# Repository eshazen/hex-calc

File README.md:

# hex-calc

Simple Hex/Binary/Decimal calculator inspired by HP-16C and TI Programmer.

[large image](pix/front.jpg)

Features:

* Hex / Decimal / Binary display in signed or unsigned mode
  * Entire stack for 8/16 bits, two levels for 32 bits
* four-function two-compliment or unsigned arithmetic
* 8 / 16 / 32 / 64 bit word size
* four-level RPN stack with roll / swap

Runs on ATMeg328 at 8MHz.  Power is 4xAA batteries regulated to 5V.
Industry-standard 16x2 backlit LCD.  Three LEDs:

* Power
* f key (function/shift) active
* signed display mode

Code in <tt>src/calc_hw</tt>.

KiCAD design in <tt>keyboard-pcb</tt>.
<br>Schematic:  [keyboard-pcb.pdf](keyboard-pcb/keyboard-pcb.pdf)

See https://github.com/eshazen/calc-demo-xwin for an X-windows
app written in C which illustrates the general idea.

## Enhancements

Thinking about some added features to support fractional arithmetic
for woodworking.  Display options to round to nearest fraction (1/4,
1/8, 1/16, 1/32, 1/64) and switch between decimal inch, fraction inch
and decimal mm.  Ft/inches another useful display option.

This would involve either floating point or scaled integer math.
For this application the range is pretty limited, maybe 8 ft (~100 in)
max.

Base units could be 2.54e-6 in (1um).  100 inches would require ~25
bits.

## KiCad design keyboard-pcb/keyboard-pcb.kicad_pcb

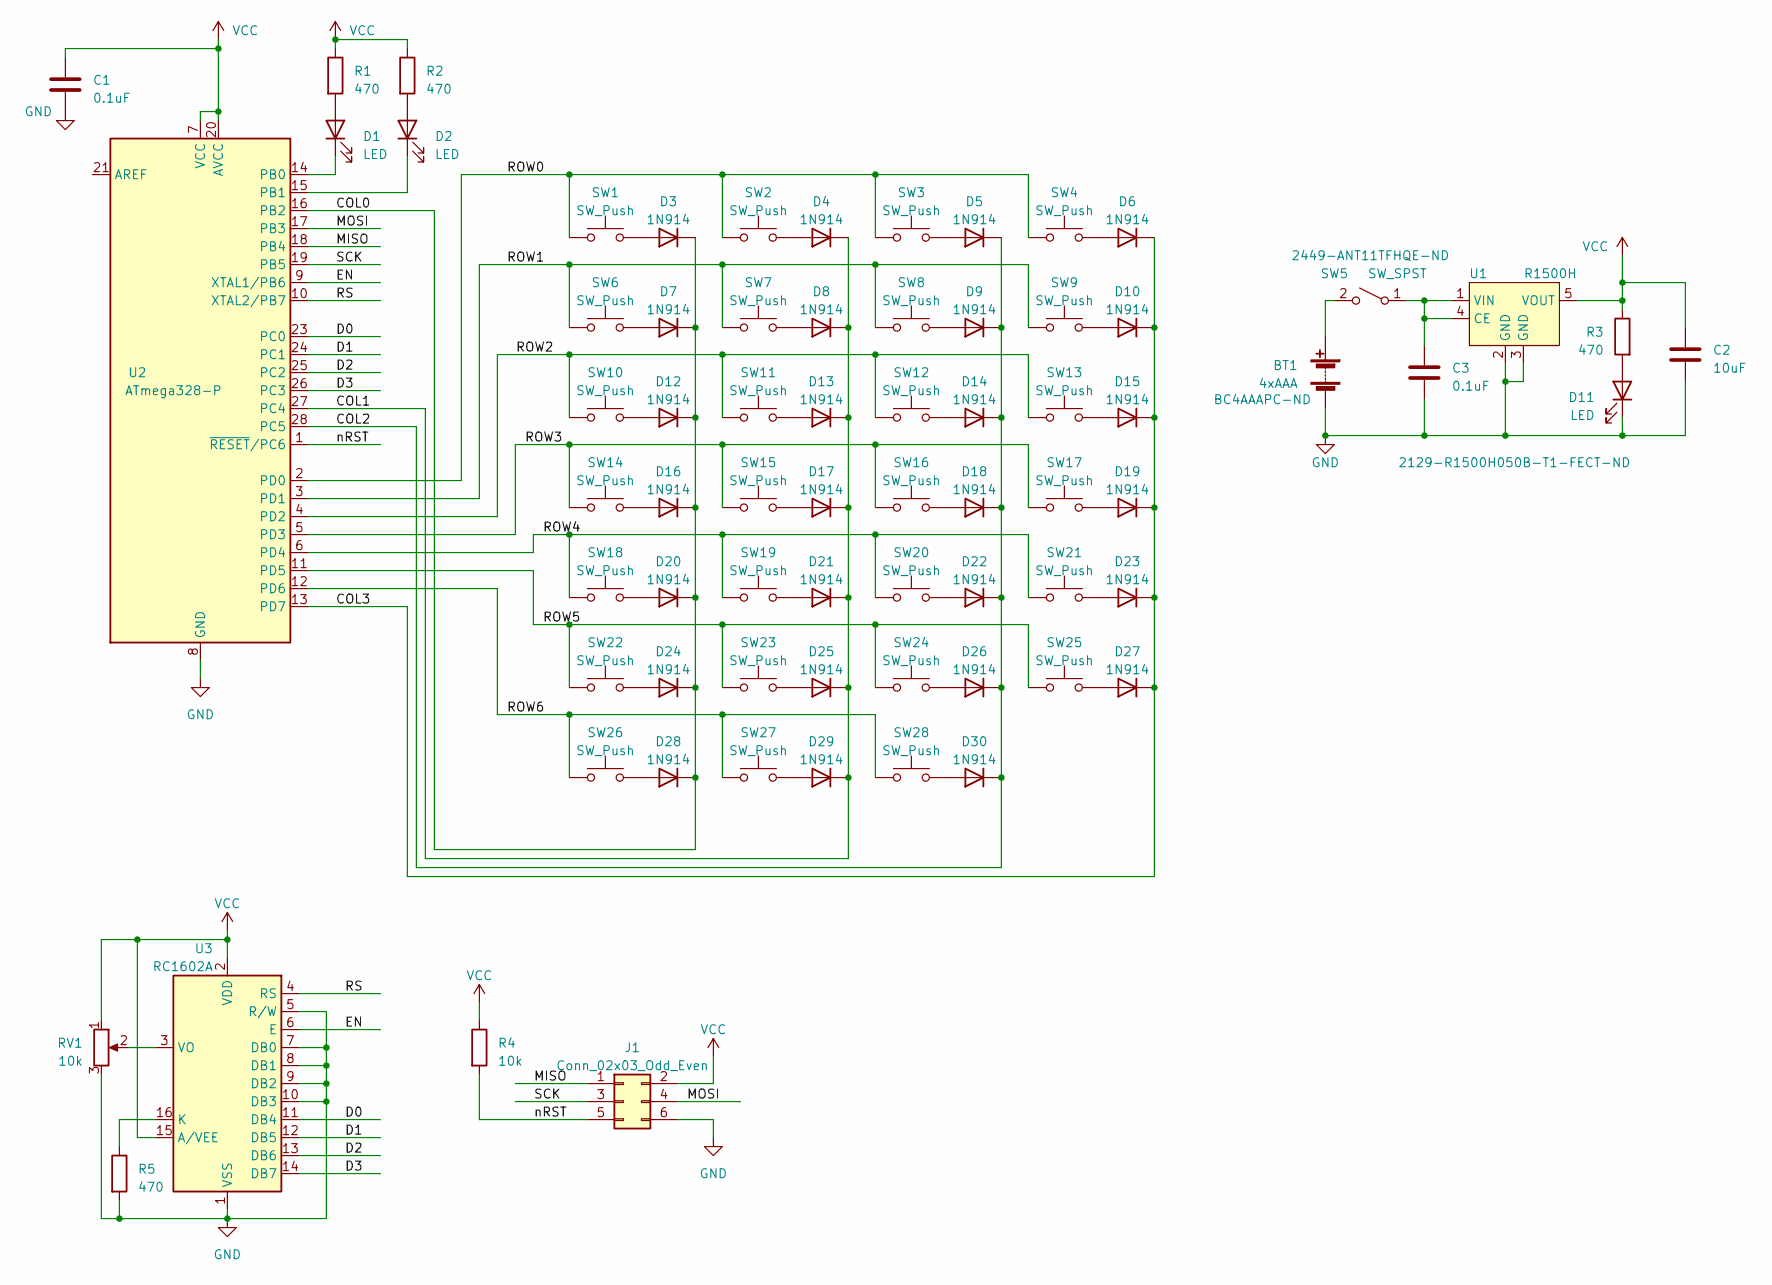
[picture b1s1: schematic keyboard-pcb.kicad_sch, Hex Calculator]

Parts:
BT1: 4xAAA; Keystone_4xAAA_2481
C1, C3: 0.1uF; C_Disc_D5.0mm_W2.5mm_P2.50mm
C2: 10uF; C_Disc_D5.0mm_W2.5mm_P2.50mm
D1, D2, D11: LED; LED_D3.0mm
D3, D4, D5, D6, D7, D8, D9, D10, D12, D13, D14, D15, D16, D17, D18, D19, D20, D21, D22, D23, D24, D25, D26, D27, D28, D29, D30: 1N914; D_DO-35_SOD27_P7.62mm_Horizontal
J1: Conn_02x03_Odd_Even; PinHeader_2x03_P2.54mm_Vertical
R1, R2, R3, R5: 470; R_Axial_DIN0207_L6.3mm_D2.5mm_P7.62mm_Horizontal
R4: 10k; R_Axial_DIN0207_L6.3mm_D2.5mm_P7.62mm_Horizontal
RV1: 10k; Potentiometer_Bourns_3266P_Horizontal
SW1, SW2, SW3, SW4, SW6, SW7, SW8, SW9, SW10, SW11, SW12, SW13, SW14, SW15, SW16, SW17, SW18, SW19, SW20, SW21, SW22, SW23, SW24, SW25, SW26, SW27: SW_Push; SW_Cherry_MX_1.00u_PCB
SW5: SW_SPST; ANT11TFHQE_switch
SW28: SW_Push; SW_Cherry_MX_2.00u_PCB
U1: R1500H; SOT-89-5_Handsoldering
U2: ATmega328-P; DIP-28_W7.62mm
U3: RC1602A; WC1602A

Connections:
/COL0: D3.1 (K), D7.1 (K), D12.1 (K), D16.1 (K), D20.1 (K), D24.1 (K), D28.1 (K), U2.16 (PB2)
/COL1: D4.1 (K), D8.1 (K), D13.1 (K), D17.1 (K), D21.1 (K), D25.1 (K), D29.1 (K), U2.27 (PC4)
/COL2: D5.1 (K), D9.1 (K), D14.1 (K), D18.1 (K), D22.1 (K), D26.1 (K), D30.1 (K), U2.28 (PC5)
/COL3: D6.1 (K), D10.1 (K), D15.1 (K), D19.1 (K), D23.1 (K), D27.1 (K), U2.13 (PD7)
/D0: U2.23 (PC0), U3.11 (DB4)
/D1: U2.24 (PC1), U3.12 (DB5)
/D2: U2.25 (PC2), U3.13 (DB6)
/D3: U2.26 (PC3), U3.14 (DB7)
/EN: U2.9 (XTAL1/PB6), U3.6 (E)
/MISO: J1.1, U2.18 (PB4)
/MOSI: J1.4, U2.17 (PB3)
/ROW0: SW1.1, SW2.1, SW3.1, SW4.1, U2.2 (PD0)
/ROW1: SW6.1, SW7.1, SW8.1, SW9.1, U2.3 (PD1)
/ROW2: SW10.1, SW11.1, SW12.1, SW13.1, U2.4 (PD2)
/ROW3: SW14.1, SW15.1, SW16.1, SW17.1, U2.5 (PD3)
/ROW4: SW18.1, SW19.1, SW20.1, SW21.1, U2.6 (PD4)
/ROW5: SW22.1, SW23.1, SW24.1, SW25.1, U2.11 (PD5)
/ROW6: SW26.1, SW27.1, SW28.1, U2.12 (PD6)
/RS: U2.10 (XTAL2/PB7), U3.4 (RS)
/SCK: J1.3, U2.19 (PB5)
/nRST: J1.5, R4.2, U2.1 (~RESET/PC6)
GND: BT1.2 (-), C1.2, C2.2, C3.2, D11.1 (K), J1.6, R5.2, RV1.3, U1.2 (GND), U1.3 (GND), U2.8 (GND), U2.22 (GND), U3.1 (VSS), U3.5 (R/W), U3.7 (DB0), U3.8 (DB1), U3.9 (DB2), U3.10 (DB3)
unnamed: BT1.1 (+), SW5.2 (B)
unnamed: D1.2 (A), R1.2
unnamed: D1.1 (K), U2.14 (PB0)
unnamed: D2.2 (A), R2.2
unnamed: D2.1 (K), U2.15 (PB1)
unnamed: D3.2 (A), SW1.2
unnamed: D4.2 (A), SW2.2
unnamed: D5.2 (A), SW3.2
unnamed: D6.2 (A), SW4.2
unnamed: D7.2 (A), SW6.2
unnamed: D8.2 (A), SW7.2
unnamed: D9.2 (A), SW8.2
unnamed: D10.2 (A), SW9.2
unnamed: D11.2 (A), R3.2
unnamed: D12.2 (A), SW10.2
unnamed: D13.2 (A), SW11.2
unnamed: D14.2 (A), SW12.2
unnamed: D15.2 (A), SW13.2
unnamed: D16.2 (A), SW14.2
unnamed: D17.2 (A), SW15.2
unnamed: D18.2 (A), SW16.2
unnamed: D19.2 (A), SW17.2
unnamed: D20.2 (A), SW18.2
unnamed: D21.2 (A), SW19.2
unnamed: D22.2 (A), SW20.2
unnamed: D23.2 (A), SW21.2
unnamed: D24.2 (A), SW22.2
unnamed: D25.2 (A), SW23.2
unnamed: D26.2 (A), SW24.2
unnamed: D27.2 (A), SW25.2
unnamed: D28.2 (A), SW26.2
unnamed: D29.2 (A), SW27.2
unnamed: D30.2 (A), SW28.2
unnamed: C3.1, SW5.1 (A), U1.1 (VIN), U1.4 (CE)
unnamed: R5.1, U3.16 (K)
unnamed: RV1.2, U3.3 (VO)
VCC: C1.1, C2.1, J1.2, R1.1, R2.1, R3.1, R4.1, RV1.1, U1.5 (VOUT), U2.7 (VCC), U2.20 (AVCC), U3.2 (VDD), U3.15 (A/VEE)

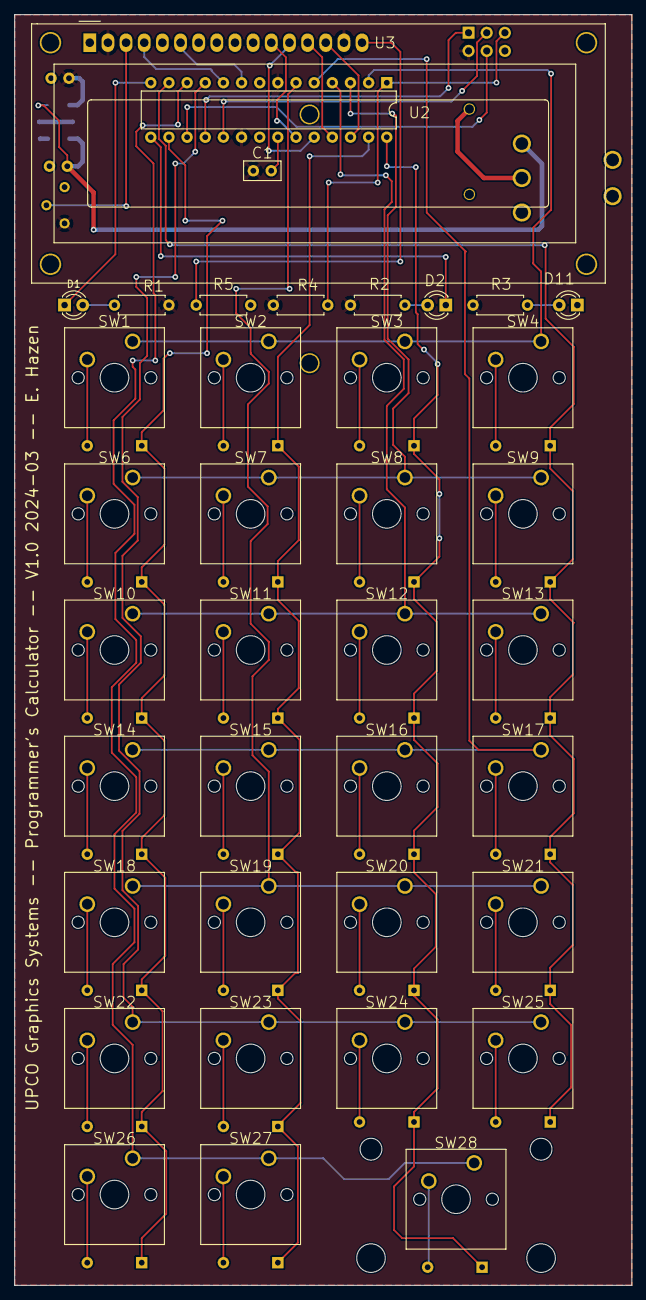
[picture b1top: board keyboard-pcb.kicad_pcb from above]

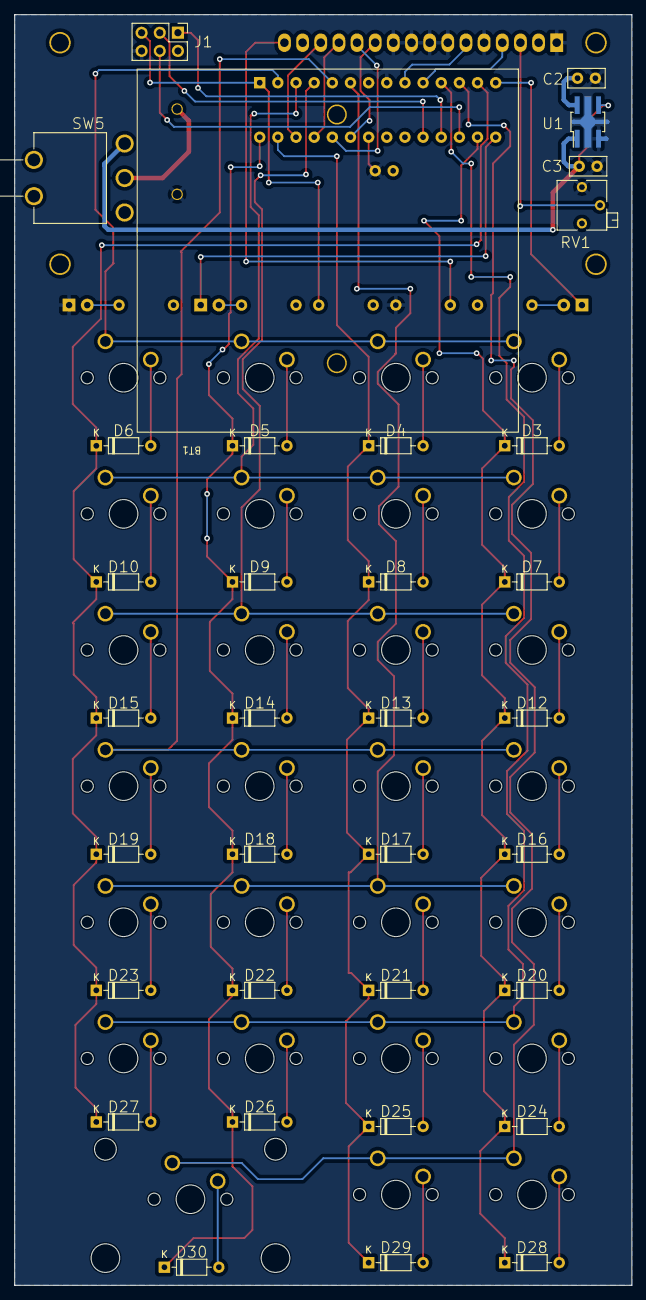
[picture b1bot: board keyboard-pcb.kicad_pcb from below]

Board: 2 copper layers, 86.4 x 177.8 mm, 72 parts (34 on the bottom side), 59 nets.

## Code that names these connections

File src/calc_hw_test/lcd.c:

#include <avr/io.h>
#include <util/delay.h>
#include "lcd.h"

//
// LCD Pinout
//
// RS   - PB7
// R/W  - GND
// E    - PB6
// D4   - PC0
// D5   - PC1
// D6   - PC2
// D7   - PC3
//

#define LCD_DATA_PORT PORTC
#define LCD_DATA_DDR DDRC
#define LCD_DATA_D0_BIT 0
#define LCD_DATA_MASK 0xf

#define LCD_CTRL_PORT PORTB
#define LCD_CTRL_DDR DDRB
#define LCD_EN_BIT 6
#define LCD_RS_BIT 7

void lcd_init( void)
{
  io_init();
  _delay_ms(15);
  send_nibble( 0, 0b0010);
  _delay_ms(5);

  send_nibble(0,0b0010);   //Function set, 4 bit
  send_nibble(0,0b1000);
 
  send_nibble(0,0b0000);   //Display ON, Cursor On, Cursor Blinking
  send_nibble(0,0b1111);

  send_nibble(0,0b0000);   //Clear Display
  send_nibble(0,0b0001);
 
  send_nibble(0,0b0000);  //Entry Mode, Increment cursor position, No display shift
  send_nibble(0,0b0110);
}

void lcd_cls( void)
{
  send_nibble(0,0b0000);   //Clear Display
  send_nibble(0,0b0001);

  lcd_addr( 0);
}
 
void lcd_putc( char c) {
  volatile unsigned char z;	/* why? */
  z = (c >> 4) & 0xf;
  send_nibble( 1, z);
  z = c & 0xf;
  send_nibble( 1, z);
}

// set address.  0=home 
void lcd_addr( uint8_t addr)
{
  volatile uint8_t z;
  z = ((addr >> 4) & 7) | 8;
  send_nibble( 0, z);
  z = addr & 0xf;
  send_nibble( 0, z);
}

void lcd_puts( char *str) {
  volatile char *p = str;	/* why volatile? */
  
  while( *p) {
    lcd_putc( *p);
    ++p;
  }
}

void io_init( void)
{
  LCD_DATA_DDR |= LCD_DATA_MASK;
  LCD_CTRL_DDR |= _BV( LCD_EN_BIT) | _BV( LCD_RS_BIT);
} 


void send_nibble( unsigned char __rs, unsigned char __data)
{
  LCD_DATA_PORT = (__data << LCD_DATA_D0_BIT); /* assert data */
  LCD_CTRL_PORT = (__rs << LCD_RS_BIT) | _BV(LCD_EN_BIT); /* set RS=H & EN=H */
  _delay_ms(1);
  LCD_CTRL_PORT = (__rs << LCD_RS_BIT); /* set RS=H and EN=L */
  _delay_ms(1);
}

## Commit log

2023-04-04 initial commit with just ideas
2023-04-04 3D model
2023-04-26 starting cherry keyboard
2023-04-26 placement in progress
2023-04-26 placement
2023-04-27 working on placement
2023-04-27 starting software
2023-04-27 working on tty version
2023-04-27 more or less working in tty mode
2023-04-28 working on AVR version
2023-04-28 semi-working AVR version
2023-04-28 placement done?
2023-05-17 change to AAA, software updates
2023-05-17 V1 ready to order?
2024-03-28 add 3D cherry model
2024-03-31 Rev1 PCB as built; debugging keyboard software
2024-03-31 calc_hw_test working
2024-04-01 Initial calc code on target, few bugs
2024-04-02 debugging code
2024-04-02 readme
2024-04-04 debugging
2024-04-05 mechanics
2024-04-05 labels
2024-04-06 still debugging
2024-04-07 fixed insert_every() but unknown issue
2024-04-08 basically working first version
2024-04-08 photo
2024-09-25 test update README
2024-09-25 commit test
2025-04-24 V0.2 improve keyboard debounce (still not perfect)
2025-05-30 add schematic PDF
